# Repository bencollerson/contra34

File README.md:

# Contra34
Fork of the Contra with 34 keys.

Also moved the microcontroller to the front to make the keyboard sit lower.

Can be flashed in QMK as a contra keyboard. Just don't assign any keys to the 14 missing keys.

# Contra
Extremely low cost ortholinear keyboard

The bare minimum for a functional keyboard.

#### In light of recent claims that I am 100% liable for any of my open source PCBs, I am adding this disclaimer.
#### I provide these PCBs as a reference for designing keyboard PCBs. Using them within your projects will require a will to do research of one's own and to learn the workings of them, potentially fixing issues if they exist.
# I provide these PCBs without liability and without any guarantees regarding functionality, as expressed in the MIT license under which all of these PCBs are licensed.

### Features
- 2U or split space.
- All through-hole parts. 48x diodes, 1x Pro Micro.
- Assembled by M2 standoffs and screws.
- Programmable via firmware of choice, such as TMK.
- Nothing fancy. A very nice way to try out some switches, enjoy some DIY, or to test out ortho keyboards.

### Parts list
- 48x 1N4148 diodes or similar, THT
- 1x Pro Micro
- 48x Switches
- Optional 1x 2U stabilizer, PCB mount
- One PCB, one plate, and one bottom plate
- 5 M2 8mm standoffs
- 10 M2 screws

### Files for production
- Main PCB: Check the [latest releases](https://github.com/ai03-2725/Contra/releases), or grab the latest gerber [here](https://github.com/ai03-2725/Contra/blob/master/Gerbers/Gerbers.zip).
- Case files: Check the case repo [here](https://github.com/ai03-2725/ContraPlates).

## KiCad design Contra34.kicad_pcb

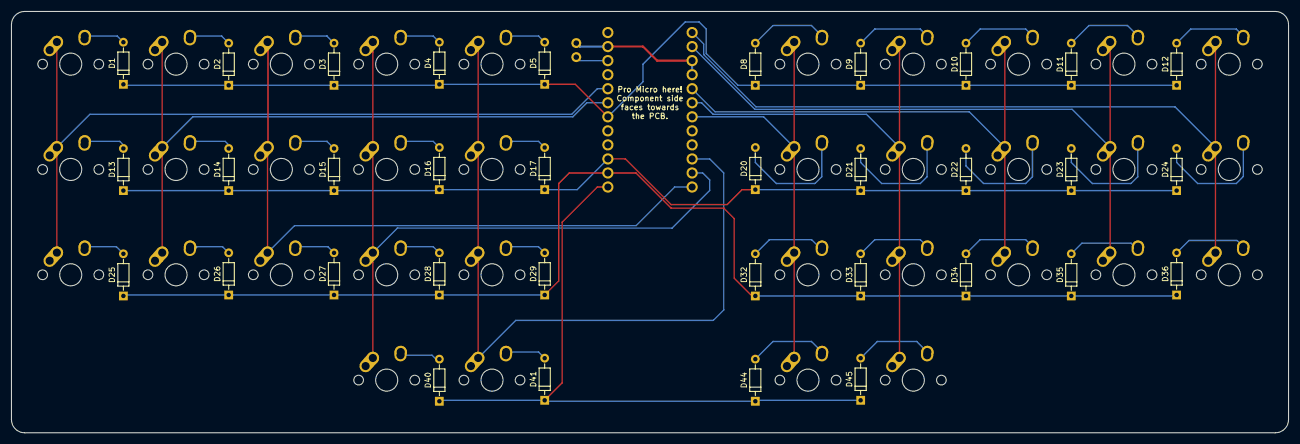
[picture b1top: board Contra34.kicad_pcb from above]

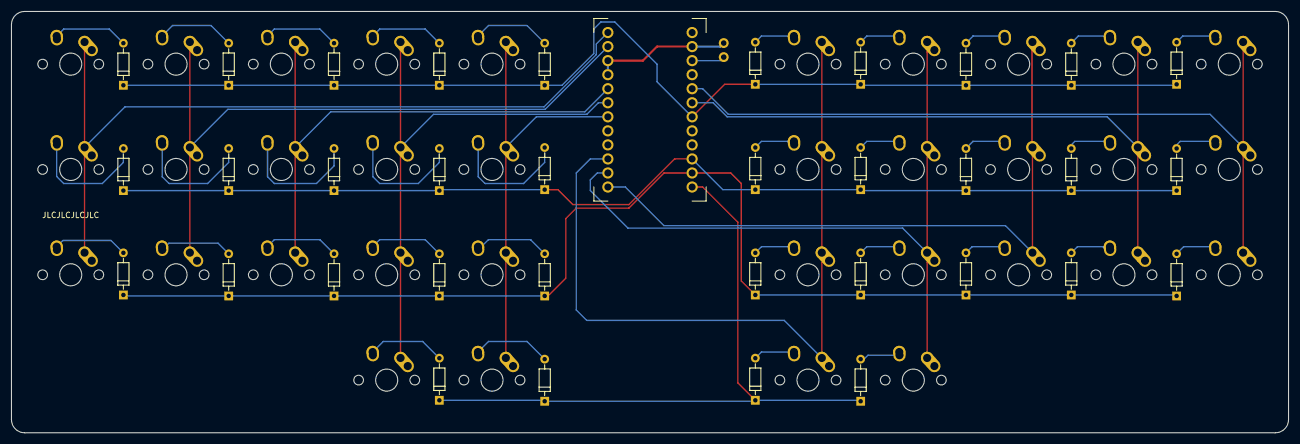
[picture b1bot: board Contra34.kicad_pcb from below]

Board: 2 copper layers, 231.0 x 76.2 mm, 70 parts (2 on the bottom side), 50 nets.

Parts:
D1, D2, D3, D4, D5, D8, D9, D10, D11, D12, D13, D14, D15, D16, D17, D20, D21, D22, D23, D24, D25, D26, D27, D28, D29, D32, D33, D34, D35, D36, D40, D41, D44, D45: 1N4148; D_DO-35_SOD27_P7.62mm_Horizontal-DoubleSided
MX1, MX2, MX3, MX4, MX5, MX8, MX9, MX10, MX11, MX12, MX13, MX14, MX15, MX16, MX17, MX20, MX21, MX22, MX23, MX24, MX25, MX26, MX27, MX28, MX29, MX32, MX33, MX34, MX35, MX36, MX40, MX41, MX44, MX45: MX-1U; MX-1U-NoLED
SW1: RESET; PushButton_6x6mm_TH_Pretty
U1: ProMicro; pro_micro

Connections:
COL0: MX1.1, MX13.1, MX25.1, U1.20
COL1: MX2.1, MX14.1, MX26.1, U1.19
COL2: MX3.1, MX15.1, MX27.1, U1.12
COL3: MX4.1, MX16.1, MX28.1, MX40.1, U1.11
COL4: MX5.1, MX17.1, MX29.1, MX41.1, U1.10
COL7: MX8.1, MX20.1, MX32.1, MX44.1, U1.7
COL8: MX9.1, MX21.1, MX33.1, MX45.1, U1.6
COL9: MX10.1, MX22.1, MX34.1, U1.5
COL10: MX11.1, MX23.1, MX35.1, U1.2
COL11: MX12.1, MX24.1, MX36.1, U1.1
GND: SW1.2, U1.3, U1.4, U1.23
unnamed: D1.2, MX1.2
unnamed: D2.2, MX2.2
unnamed: D3.2, MX3.2
unnamed: D4.2, MX4.2
unnamed: D5.2, MX5.2
unnamed: D8.2, MX8.2
unnamed: D9.2, MX9.2
unnamed: D10.2, MX10.2
unnamed: D11.2, MX11.2
unnamed: D12.2, MX12.2
unnamed: D13.2, MX13.2
unnamed: D14.2, MX14.2
unnamed: D15.2, MX15.2
unnamed: D16.2, MX16.2
unnamed: D17.2, MX17.2
unnamed: D20.2, MX20.2
unnamed: D21.2, MX21.2
unnamed: D22.2, MX22.2
unnamed: D23.2, MX23.2
unnamed: D24.2, MX24.2
unnamed: D25.2, MX25.2
unnamed: D26.2, MX26.2
unnamed: D27.2, MX27.2
unnamed: D28.2, MX28.2
unnamed: D29.2, MX29.2
unnamed: D32.2, MX32.2
unnamed: D33.2, MX33.2
unnamed: D34.2, MX34.2
unnamed: D35.2, MX35.2
unnamed: D36.2, MX36.2
unnamed: D40.2, MX40.2
unnamed: D41.2, MX41.2
unnamed: D44.2, MX44.2
unnamed: D45.2, MX45.2
unnamed: SW1.1, U1.22
ROW0: D1.1, D2.1, D3.1, D4.1, D5.1, D8.1, D9.1, D10.1, D11.1, D12.1, U1.18
ROW1: D13.1, D14.1, D15.1, D16.1, D17.1, D20.1, D21.1, D22.1, D23.1, D24.1, U1.15
ROW2: D25.1, D26.1, D27.1, D28.1, D29.1, D32.1, D33.1, D34.1, D35.1, D36.1, U1.14
ROW3: D40.1, D41.1, D44.1, D45.1, U1.13

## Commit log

2022-10-22 Modified contra keyboard with 34 keys.
    features:
    * 34 key layout
    * top-mounted microcontroller
    * lower profile
    * "half plate" for each set of keys
2023-06-16 add a photo
